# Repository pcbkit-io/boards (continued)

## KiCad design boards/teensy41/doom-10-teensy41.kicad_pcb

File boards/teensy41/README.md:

# 10 · teensy41 — Cortex-M7 at 600 MHz: Doom at full speed, Doom II too

The most capable variant: a Teensy 4.1 (NXP i.MX RT1062) on sockets behind a 3.5" 320 × 480 touch
TFT, ten buttons, CD-quality audio to headphones and a speaker, and two 18650 cells with protection,
a power-path charger on USB-C, a fuel gauge and a 5 V boost. JLCPCB assembles everything but the two
modules (and the speaker), which plug into the sockets and the connector it solders. The i.MX RT1062 is a BGA-196 crossover MCU with external flash; the Teensy module is
how hobbyists (and small products) use it without a 6-layer BGA board.

| | |
|---|---|
| Processor | Teensy 4.1: NXP i.MX RT1062, Arm **Cortex-M7** (ARMv7E-M, 6-stage dual-issue, double-precision FPU, 32 KB I + 32 KB D cache) at 600 MHz; 1 MB SRAM (512 KB tightly coupled ITCM/DTCM); 8 MB QSPI flash (FlexSPI); pads for 8 MB PSRAM (FlexSPI2); microSD socket on 4-bit SDIO (uSDHC1) |
| Display | 3.5" 320 × 480 ILI9488 + XPT2046 touch (MSP3520) on LPSPI4 (D13 SCK, D11 MOSI, D12 MISO, D10 CS, D9 DC, D8 RESET, D6 backlight PWM; touch CS D5, IRQ D4) |
| Input | 10 × 6 mm tact switches: D0–D3, D14–D17, D22, D24 |
| Sound | SAI1 I2S (D21 BCLK, D20 LRCLK, D7 TX) → **PCM5102A** → 3.5 mm jack and → **PAM8403** (shutdown on D26) → 8 Ω speaker |
| Power | 2 × 18650 Li-ion in parallel (1S2P) behind reverse-cell (AO3401A) and DW01A + FS8205A protection; USB-C (charging only, 1 A PTC fuse, TVS) → **BQ24075** power path (SYS); **MAX17048** fuel gauge (D18 SDA, D19 SCL, alert D25); **TPS61023** boost SYS → 5 V (switched by the on/off switch on its EN) → 1N5819HW → Teensy VIN (VIN and VUSB are joined on the Teensy: the diode keeps the boost and a USB host apart) |
| Programming | the Teensy's micro-USB (not the charging USB-C): **Teensy Loader** / `teensy_loader_cli` talking to its MKL02 bootloader chip (HalfKay); the program button forces it |
| Board | 172 × 112 mm, **4 layers**, four M3 holes; front: display, buttons, on/off switch, charging USB-C, charger and boost, test pads; back: Teensy (its USB at the top edge), two 18650 holders (right of the Teensy, so its microSD card comes out), audio, speaker plug (left edge), jack (right edge) |

<!-- STATUS -->
**Board status** (measured on the dev host with PCBKit's CLI): `pcbkit check`: complete — 0 errors, 0 warnings, 0 unrouted nets. 88 components, 66 nets, 769 track segments (3204 mm), 43 vias.
`analysis.run { lens: "ready" }`: Typical scenario, partly by family estimates. Nothing to fix, 1 to consider, 14 ok: weigh the warnings (tell the person about the ones that are their choice), then the board is ready to order.
`pcbkit export --format fab` succeeds without `--force`: every assembled line of the BOM has an LCSC code.
<!-- /STATUS -->

The ready lens's notes are not faults: it estimates heat with generic package limits where the
makers publish no thermal data, and reads the Teensy's and the screen's draw from their families.
Keystone 1042 holders (C5249310) are stocked in hundreds at JLCPCB: check before ordering more than
a few boards.

## Run it in the browser

Open https://app.pcbkit.io/github/pcbkit-io/doom-handheld/tree/main/boards/teensy41, open the
Laboratory and press **Build & run**: the page builds `doom/` for the i.MX RT1062's Cortex-M7
(with `DOOM1.WAD` linked into its flash), boots it the way the chip's boot ROM boots the Teensy's
flash, and draws the ILI9488's frames on the board. Play with the keyboard (arrows, F fire, Space
use, comma/period strafe, M menu, Enter) or a gamepad (`input.js`).

## Why it runs Doom

The Cortex-M7 at 600 MHz runs Doom with time to spare; the game's data, the shareware WAD, is
linked into the Teensy's 8 MB flash with the program and read in place, so no SD card is needed.
Its 1 MB of RAM holds the rest: the program's start-up makes the FlexRAM one OCRAM with OCRAM2
(1 MB from 0x2020_0000) for the engine's state, two screens and a zone heap of about 600 KB (Doom's
shareware levels need about 576 KB, measured). For that the board's copy of the engine keeps its
trigonometric tables in flash, its visplanes' rows in bytes (as Doom's original did) and changes
screens without the melt (`doom/doom_teensy.c` says where). Each frame goes to the ILI9488 in
18-bit colour (its only format over SPI), 320 × 200 in the middle of its 480 × 320, on LPSPI4 at
33 MHz: 46 ms a frame. Measured in PCBKit's simulator: the title at 4 s of device time, the demo
at 13 s.

## Power

Two 18650 Li-ion cells in Keystone 1042 holders on the back, in parallel (1S2P, 3.0–4.2 V), the
power section of `boards/rp2350-handheld` with this board's own USB-C, boost and fuel gauge:

- **Reverse cells:** an AO3401A P-MOSFET in the plus line, its gate at the cells' minus: cells put
  in backwards leave it off and the board unpowered (it conducts both ways when they are right, so
  charging goes through it too). It cannot help one cell reversed against the other: in parallel
  they would short each other, so check both against the silkscreen's + before closing a case.
- **Protection:** DW01A + FS8205A in the pack's minus: over-charge 4.3 V, over-discharge 2.4 V,
  over-current about 3 A and short circuit, for the pack. Flat-top unprotected 18650 cells fit the
  holders.
- **Charger with power path:** a TI BQ24075 from the USB-C (5.1 kΩ on CC, a 1 A resettable fuse and
  a TVS diode on VBUS), in USB500 mode (at most 500 mA from the port), 800 mA fast charge (RISET
  1.13 kΩ), input limit set by RILIM 1.18 kΩ, safety timers off (two cells in parallel charge longer
  than its longest timer; termination is by current), TS tied to 10 kΩ (no thermistor). Its output
  SYS runs the board from USB when one is plugged in and from the cells otherwise.
- **5 V and on/off:** the TPS61023 boosts SYS to 5 V for the Teensy's VIN through a 1N5819HW; the
  slide switch on the left edge drives the boost's EN (off: the Teensy unpowered, the cells still
  charging). The speaker amplifier runs from SYS, the DAC and the screen from the Teensy's 3.3 V.
- **Fuel gauge:** a MAX17048 on the cells (after the protection) reports their charge over I2C.

| State | Current (estimate) |
|---|---|
| Teensy 4.1 at 600 MHz | ~100 mA at 5 V VIN (PJRC: about 100 mA) |
| ILI9488 3.5" with backlight | ~80–100 mA at 3.3 V |
| PCM5102A + PAM8403 | 20 + 50–200 mA |
| **Typical** | **≈ 1 W → ~300 mA at 3.7 V after the boost** |

Two 3000 mAh cells → **about 20 h** (estimate). A full charge of two empty cells at 800 mA takes
about 8 h (longer from a USB 2.0 port, which the charger limits to 500 mA).

## Charging

Plug a USB-C charger into the board's USB-C at the bottom edge (charging only; it has no data). The
red LED (CHG) is on while the cells charge and goes out when they are full; the green LED (USB) is
on while USB power is present. The board plays from USB while it charges, and charges with the
switch off. Insert the cells with + at the end the back's silkscreen marks.

## Modules plugged in by hand

The assembly solders two 1x24 female sockets, one 1x14 female socket and a JST PH speaker plug;
these are bought separately:

- **U1: Teensy 4.1** (PJRC TEENSY41, with pins soldered on), on the back, components facing the
  board, its USB at the top edge; a microSD card in its socket holds the WAD.
- **DS1: 3.5" ILI9488 SPI TFT with touch, MSP3520** (14 pins), on the front.
- **J5: an 8 Ω, 1–2 W speaker** with a 2-pin JST PH lead.

## Firmware: build and flash

- **Build:** in PCBKit, the Laboratory's **Build & run** builds `doom/` (Cortex-M7, hard float, the
  kit's flash configuration block, IVT and boot data at the start of flash); then export the
  firmware (`export.run { format: "firmware" }`): `U1.hex`.
- **Flashing on arrival:** plug the Teensy's micro-USB into a computer, open the Teensy Loader (or
  run `teensy_loader_cli --mcu=TEENSY41 -w -v U1.hex`) and press the Teensy's program button: its
  MKL02 boot loader chip writes the image; nothing on the board to configure, no programmer.

## Bill of materials

Rough cost at 10 pieces (estimates): Teensy 4.1 $31.50 · 2 × 24-pin sockets $0.80 · MSP3520 3.5"
touch module $11 · PCM5102A $2.00 · PAM8403 $0.15 · jack $0.60 · BQ24075 $1.10 · DW01A, FS8205A and
AO3401A $0.25 · MAX17048 $1.60 · TPS61023 $0.60 · USB-C $0.20 · buttons $2.90 · passives $1.50 ·
two 18650 holders $9.80 · 4-layer PCB $5.00 · speaker $1.00 · microSD card $4 → **about $75**
without the cells.

<!-- BOM -->
The assembly BOM as `pcbkit export --format fab` writes it (JLCPCB assembly: LCSC codes; the modules' lines are their sockets):

| Qty | Refs | Part | LCSC | Footprint |
|---|---|---|---|---|
| 2 | BT1, BT2 | 1042 | C5249310 | BatteryHolder_Keystone_1042_1x18650 |
| 6 | C1, C3, C5, C9, C18, C21 | 100nF | C1525 | C_0402_1005Metric |
| 4 | C2, C4, C6, C22 | 10uF | C15850 | C_0805_2012Metric |
| 2 | C7, C8 | 2.2uF | C87994 | C_0805_2012Metric |
| 2 | C10, C11 | 2.2nF | C1531 | C_0402_1005Metric |
| 4 | C12, C13, C14, C16 | 1uF | C52923 | C_0402_1005Metric |
| 3 | C15, C23, C24 | 22uF | C12891 | C_1206_3216Metric |
| 1 | C17 | 470nF | C47339 | C_0402_1005Metric |
| 1 | D1 | 1N5819HW-7-F | C82544 | D_SOD-123 |
| 1 | D2 | tvs 5V | C19224 | D_SOD-323 |
| 1 | DS1 | Female header 1x14 2.54 mm | C2905420 | TFT_3.5in_ILI9488_Socket_1x14_P2.54mm |
| 1 | F1 | PTC 1000mA | C20800 | Fuse_1206_3216Metric |
| 1 | J1 | SJ1-3525N | C4991936 | Jack_3.5mm_SameSky_SJ1-352XN_Horizontal |
| 1 | J3 | USB_C_Receptacle_USB2.0_16P | C165948 | USB_C_Receptacle_USB2.0_16P |
| 1 | J5 | S2B-PH-K-S(LF)(SN) | C173752 | JST_PH_S2B-PH-K_1x02_P2.00mm_Horizontal |
| 1 | L1 | 1uH | C96955 | L_Power_6x6mm |
| 1 | Q1 | AO3401A | C15127 | SOT-23 |
| 1 | Q2 | FS8205A | C5148694 | TSSOP-8_4.4x2.93mm_P0.65mm |
| 5 | R1, R2, R3, R4, rTs | 10kohm | C25744 | R_0402_1005Metric |
| 1 | R5 | 1Mohm | C26083 | R_0402_1005Metric |
| 2 | R6, R7 | 470ohm | C25117 | R_0402_1005Metric |
| 2 | R8, R18 | 100kohm | C25741 | R_0402_1005Metric |
| 1 | R9 | 100ohm | C25076 | R_0402_1005Metric |
| 1 | R10 | 1kohm | C11702 | R_0402_1005Metric |
| 2 | R11, R12 | 5.1kohm | C25905 | R_0402_1005Metric |
| 2 | R15, R16 | 3.3kohm | C25890 | R_0402_1005Metric |
| 1 | R17 | 732kohm | C137940 | R_0402_1005Metric |
| 10 | SW1, SW2, SW3, SW4, SW5, SW6, SW7, SW8, SW9, SW10 | PTS645SM43SMTR92 LFS | C221880 | SW_Tactile_SPST_6x6mm_SMD |
| 1 | SW12 | MSK12C02 | C431540 | SW_Slide_SPDT_Shouhan_MSK12C02 |
| 2 | U1 | Female header 1x24 2.54 mm | C41376163 | Teensy41_Socket_2x24_P2.54mm_W15.24mm |
| 1 | U2 | PCM5102APWR | C107671 | TSSOP-20_4.4x6.5mm_P0.65mm |
| 1 | U3 | PAM8403DR | C17337 | SOIC-16_3.9x9.9mm_P1.27mm |
| 1 | U4 | BQ24075RGTR | C15464 | QFN-16-1EP_3x3mm_P0.5mm_EP1.68x1.68mm |
| 1 | U5 | MAX17048G+T10 | C2682616 | DFN-8-1EP_2x2mm_P0.5mm_EP0.8x1.2mm |
| 1 | U6 | TPS61023DRLR | C919459 | SOT-563 |
| 1 | U7 | DW01A | C351410 | SOT-6_1.6x2.9mm_P0.95mm |
| 2 | cBat, cSys | 4.7uF | C1779 | C_0805_2012Metric |
| 1 | cIn | 1uF | C15849 | C_0603_1608Metric |
| 1 | ledChg | red | C2286 | LED_0603_1608Metric |
| 1 | ledPg | green | C12624 | LED_0603_1608Metric |
| 2 | rChg, rPg | 1.5kohm | C25867 | R_0402_1005Metric |
| 1 | rIlim | 1.18kohm | C270651 | R_0402_1005Metric |
| 1 | rIset | 1.13kohm | C67014 | R_0402_1005Metric |
<!-- /BOM -->

## What PCBKit's engine must model to simulate it faithfully

- **Core:** **ARMv7E-M with FPv5-D16** (double precision), plus the M7's **caches** (CCR, cache
  maintenance by address: the SDK cleans/invalidates around DMA) and **TCM** (ITCM/DTCM at 0x0 /
  0x2000_0000 with FlexRAM banks configured by `IOMUXC_GPR`); MPU regions the SDK programs.
- **Interrupt controller:** NVIC with 160 lines; SysTick; the GPT/PIT timers Teensyduino uses.
- **Boot ROM:** the i.MX RT boot ROM's **serial NOR boot**: read the FCB at 0x6000_0000 to configure
  FlexSPI, then the IVT and boot data, then jump; the image format is that header, not ELF.
- **Clocks (CCM):** ARM PLL to 600 MHz, the dividers for IPG/PERCLK, LPSPI and SAI root clocks;
  the DCDC voltage step Teensyduino performs before raising the clock.
- **Peripherals:** **IOMUXC** pin mux (every pad has a mux register and a pad-control register: the
  pin-mux table from NXP's SVD), GPIO1–9 (fast GPIO6–9 aliases), LPSPI4 + **eDMA with DMAMUX**,
  **SAI1** (I2S) + eDMA, LPI2C1, **uSDHC1** (SD 4-bit with ADMA2 descriptors), USB OTG (the bootloader
  is a separate chip: flashing can be modelled as writing the image directly).
- **Board:** ILI9488 (18-bit pixel format over SPI) + XPT2046, SD card in SD mode, PCM5102A, BQ24075,
  MAX17048, two 18650 cells as a discharge curve, a boost into VIN behind a diode.

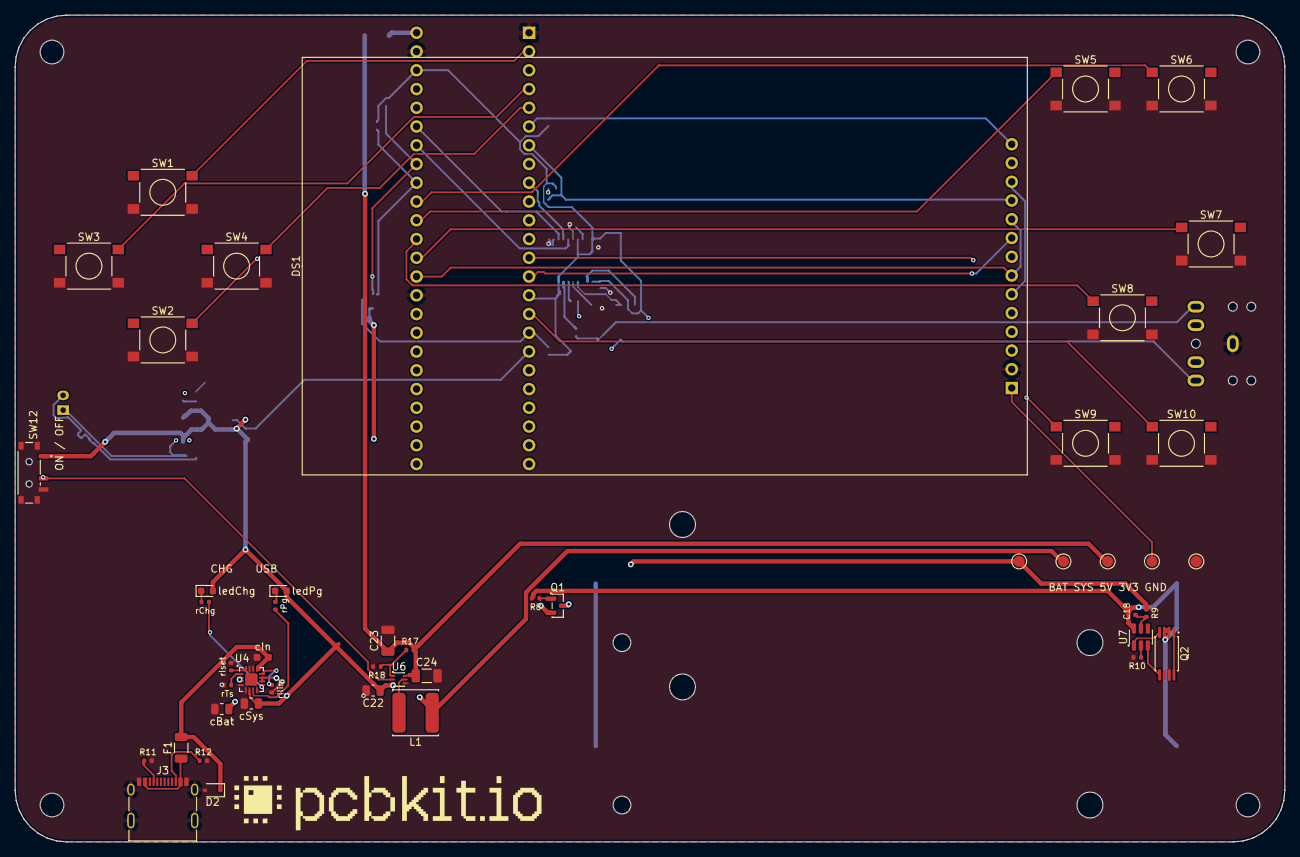
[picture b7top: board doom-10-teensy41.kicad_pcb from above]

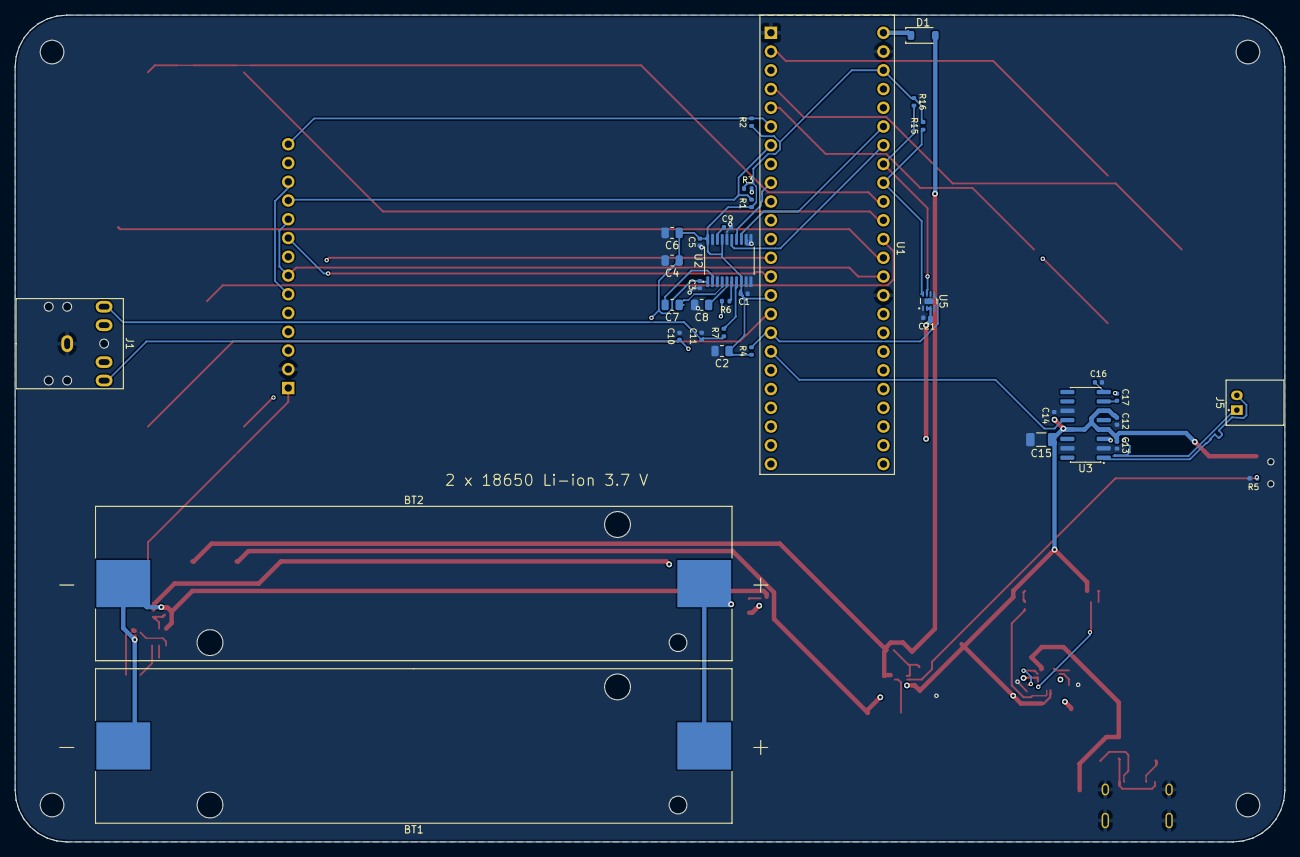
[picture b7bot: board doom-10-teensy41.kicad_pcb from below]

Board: 4 copper layers, 172.0 x 112.0 mm, 88 parts (36 on the bottom side), 66 nets.

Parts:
BT1, BT2: 1042; BatteryHolder_Keystone_1042_1x18650
C1, C3, C5, C9, C18, C21: 100nF; C_0402_1005Metric
C2, C4, C6, C22: 10uF; C_0805_2012Metric
C7, C8: 2.2uF; C_0805_2012Metric
C10, C11: 2.2nF; C_0402_1005Metric
C12, C13, C14, C16: 1uF; C_0402_1005Metric
C15, C23, C24: 22uF; C_1206_3216Metric
C17: 470nF; C_0402_1005Metric
D1: 1N5819HW-7-F; D_SOD-123
D2: tvs 5V; D_SOD-323
DS1: MSP3520 3.5in 320x480 SPI TFT module with touch (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; TFT_3.5in_ILI9488_Socket_1x14_P2.54mm
F1: PTC 1000mA; Fuse_1206_3216Metric
H1, H2, H3, H4: MountingHole_3.2mm_M3
J1: SJ1-3525N; Jack_3.5mm_SameSky_SJ1-352XN_Horizontal
J3: USB_C_Receptacle_USB2.0_16P
J5: S2B-PH-K-S(LF)(SN); JST_PH_S2B-PH-K_1x02_P2.00mm_Horizontal
L1: 1uH; L_Power_6x6mm
Q1: AO3401A; SOT-23
Q2: FS8205A; TSSOP-8_4.4x2.93mm_P0.65mm
R1, R2, R3, R4: 10kohm; R_0402_1005Metric
R5: 1Mohm; R_0402_1005Metric
R6, R7: 470ohm; R_0402_1005Metric
R8, R18: 100kohm; R_0402_1005Metric
R9: 100ohm; R_0402_1005Metric
R10: 1kohm; R_0402_1005Metric
R11, R12: 5.1kohm; R_0402_1005Metric
R15, R16: 3.3kohm; R_0402_1005Metric
R17: 732kohm; R_0402_1005Metric
SW1, SW2, SW3, SW4, SW5, SW6, SW7, SW8, SW9, SW10: PTS645SM43SMTR92 LFS; SW_Tactile_SPST_6x6mm_SMD
SW12: MSK12C02; SW_Slide_SPDT_Shouhan_MSK12C02
U1: TEENSY41; Teensy41_Socket_2x24_P2.54mm_W15.24mm
U2: PCM5102APWR; TSSOP-20_4.4x6.5mm_P0.65mm
U3: PAM8403DR; SOIC-16_3.9x9.9mm_P1.27mm
U4: BQ24075RGTR; QFN-16-1EP_3x3mm_P0.5mm_EP1.68x1.68mm
U5: MAX17048G+T10; DFN-8-1EP_2x2mm_P0.5mm_EP0.8x1.2mm
U6: TPS61023DRLR; SOT-563
U7: DW01A; SOT-6_1.6x2.9mm_P0.95mm
cBat: 4.7uF; C_0805_2012Metric
cIn: 1uF; C_0603_1608Metric
cSys: 4.7uF; C_0805_2012Metric
ledChg: red; LED_0603_1608Metric
ledPg: green; LED_0603_1608Metric
logo: Logo_PCBKit_pcbkit.io
rChg: 1.5kohm; R_0402_1005Metric
rIlim: 1.18kohm; R_0402_1005Metric
rIset: 1.13kohm; R_0402_1005Metric
rPg: 1.5kohm; R_0402_1005Metric
rTs: 10kohm; R_0402_1005Metric
tpBat: TestPoint_Round_D1.5mm
tpGnd: TestPoint_Round_D1.5mm
tpSys: TestPoint_Round_D1.5mm
tpV3, tpV5: TestPoint_Round_D1.5mm

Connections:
AMP_SD: U1.18, U3.12
BAT: C21.1, Q1.2, R9.1, U4.2, U4.3, U5.2, U5.3, cBat.1, tpBat.1
BAT_IN: BT1.2, BT2.2, Q1.3
BOOST_EN: R5.1, SW12.2, U6.2
CELL_N: BT1.1, BT2.1, C18.2, Q2.2, Q2.3, R8.2, U7.6
CHG_LED: ledChg.1, rChg.2
CHG_N: U4.9, rChg.1
DAC_LDO: C9.1, U2.18
DAC_VNEG: C8.1, U2.5
DOWN: SW2.1, SW2.2, U1.3
ENTER: SW10.1, SW10.2, U1.16
FIRE: SW7.1, SW7.2, U1.37
FUEL_ALRT: R4.2, U1.17, U5.5
GND: C1.2, C2.2, C3.2, C4.2, C5.2, C6.2, C8.2, C9.2, C10.2, C11.2, C12.2, C13.2, C14.2, C15.2, C16.2, C21.2, C22.2, C23.2, C24.2, D2.2, DS1.2, J1.1, J3.A1, J3.B1, J3.S1, Q2.6, Q2.7, R5.2, R10.2, R11.2, R12.2, R18.2, SW1.3, SW1.4, SW2.3, SW2.4, SW3.3, SW3.4, SW4.3, SW4.4, SW5.3, SW5.4, SW6.3, SW6.4, SW7.3, SW7.4, SW8.3, SW8.4, SW9.3, SW9.4, SW10.3, SW10.4, SW12.3, SW12.4, U1.1, U1.26, U1.39, U2.3, U2.9, U2.10, U2.11, U2.12, U2.16, U2.19, U3.2, U3.11, U3.15, U4.4, U4.5, U4.8, U4.14, U4.15, U4.17, U5.1, U5.4, U5.6, U5.9, U6.4, cBat.2, cIn.2, cSys.2, rIlim.2, rIset.2, rTs.2, tpGnd.1
I2S_BCK: U1.30, U2.13
I2S_DIN: U1.9, U2.14
I2S_LRCK: U1.31, U2.15
ILIM: U4.12, rIlim.1
ISET: U4.16, rIset.1
LCD_BL: DS1.8, U1.8
LCD_CS: DS1.3, R3.2, U1.12
LCD_DC: DS1.5, U1.11
LCD_RST: DS1.4, U1.10
LEFT: SW3.1, SW3.2, U1.4
LINE_L: C10.1, C17.1, J1.2, R6.2
LINE_R: C11.1, J1.3, R7.1
MENU: SW9.1, SW9.2, U1.29
MISO: DS1.9, DS1.13, U1.14
MOSI: DS1.6, DS1.12, U1.13
unnamed: C7.2, U2.2
unnamed: C7.1, U2.4
unnamed: C16.1, U3.8
unnamed: C17.2, U3.7
unnamed: C18.1, R9.2, U7.5
unnamed: L1.2, U6.5
unnamed: Q2.4, U7.1
unnamed: Q2.5, U7.3
unnamed: R6.1, U2.6
unnamed: R7.2, U2.7
unnamed: R10.1, U7.2
unnamed: R17.1, R18.1, U6.1
PG_LED: ledPg.1, rPg.1
PG_N: U4.7, rPg.2
RIGHT: SW4.1, SW4.2, U1.5
SCK: DS1.7, DS1.10, U1.38
SCL: R16.2, U1.32, U5.7
SDA: R15.1, U1.33, U5.8
SPK_N: J5.1, U3.3
SPK_P: J5.2, U3.1
STRAFE_L: SW5.1, SW5.2, U1.35
STRAFE_R: SW6.1, SW6.2, U1.34
SYS: C12.1, C13.1, C14.1, C15.1, C22.1, L1.1, SW12.1, U3.4, U3.6, U3.13, U4.6, U4.10, U4.11, U6.3, cSys.1, ledChg.2, ledPg.2, tpSys.1
TS: U4.1, rTs.1
T_CS: DS1.11, R1.2, U1.7
T_IRQ: DS1.14, R2.2, U1.6
U7Support/DRAIN: Q2.1, Q2.8
UP: SW1.1, SW1.2, U1.2
USE: SW8.1, SW8.2, U1.36
V3: C1.1, C2.1, C3.1, C4.1, C5.1, C6.1, DS1.1, R1.1, R2.1, R3.1, R4.1, R15.2, R16.1, U1.15, U1.27, U2.1, U2.8, U2.17, U2.20, tpV3.1
V5: C23.1, C24.1, D1.2, R17.2, U6.6, tpV5.1
VBUS: D2.1, F1.2, U4.13, cIn.1
VIN: D1.1, U1.25
reversed/gate: Q1.1, R8.1
usb/cc1: J3.A5, R11.1
usb/cc2: J3.B5, R12.1
usb/raw: F1.1, J3.A4, J3.B4

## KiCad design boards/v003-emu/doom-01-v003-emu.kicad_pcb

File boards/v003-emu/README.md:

# 01 · v003-emu — Doom on a 10-cent RISC-V, by emulation

The most primitive variant: a WCH CH32V003 cannot hold Doom (2 KB of RAM), so it does not try.
Its firmware is a small RV32IMA interpreter; the real program — Doom built for a plain RV32 machine
— lives in an 8 MB SPI PSRAM and boots from a 16 MB SPI flash. It is the "Linux on an 8-bit AVR"
trick applied to Doom: slow (well under one frame per second, estimate below), but every part is a
real, orderable chip, and it is the clearest test of whether PCBKit's engine models *buses* rather
than *programs*.

| | |
|---|---|
| Processor | WCH CH32V003F4P6, QingKe V2A core: RISC-V **RV32EC** (16 registers, compressed) + WCH's XW byte/halfword extension, 48 MHz (24 MHz HSI × 2 PLL), 2 KB SRAM, 16 KB flash, TSSOP-20 |
| Memory | APS6404L-3SQR 8 MB PSRAM (guest RAM) and W25Q128JV 16 MB NOR flash (guest kernel + WAD), both on SPI1 (PC5/PC6/PC7) with their own chip selects (PC0, PC4) |
| Display | Nokia 5110 module, PCD8544, 84 × 48 monochrome, SPI shared with the memories (CS PC3, D/C PC2), reset by RC at power-up |
| Input | 8 tact switches (5.1 mm) to GND, internal pull-ups: PD0, PD2–PD6, PA1, PA2 (the crystal pins are free: the HSI runs the chip) |
| Sound | passive piezo on PC1 (TIM2 CH4 remap) |
| Power | 2 × 18650 Li-ion in parallel (1S2P) behind reverse-cell (AO3401A) and DW01A + FS8205A protection; BQ24075 charger with power path from a USB-C port (fuse, TVS); SYS → AP2112K-3.3 LDO, its enable on the slide switch |
| Programming | WCH single-wire debug (SDI) on PD1: J2, a 3-pin header (3V3, SWIO, GND) at the right edge of the back for a WCH-LinkE |
| Board | 96 × 92 mm, 2 layers, four M3 holes; front: LCD, buttons, USB-C, charger, switch, test pads; back: two 18650 holders, the processor and its memories, piezo, J2 |

<!-- STATUS -->
**Board status** (measured on the dev host with PCBKit's CLI): `pcbkit check`: complete — 0 errors, 0 warnings, 0 unrouted nets. 67 components, 46 nets, 439 track segments (1295 mm), 38 vias.
`analysis.run { lens: "ready" }`: Typical scenario, partial. Nothing to fix, 1 to consider, 15 ok: weigh the warnings (tell the person about the ones that are their choice), then the board is ready to order.
`pcbkit export --format fab` succeeds without `--force`: every assembled line of the BOM has an LCSC code.
<!-- /STATUS -->

## Run it in the browser

Open https://app.pcbkit.io/github/pcbkit-io/doom-handheld/tree/main/boards/v003-emu, open the
Laboratory and press **Build & run**: the page builds both programs — `emu/` for the CH32V003
(RV32EC) and `doom/` for the computer it emulates (pcbkit-virt, with `DOOM1.WAD` linked in) — puts
the second in the W25Q128 and runs the board. Until the first frame the LCD shows Doom's start-up
messages; the title screen comes after about three minutes of device time, then the demo.

## Why it can (barely) run Doom

The CH32V003's job is only to be a CPU for an emulated one (`emu/`):

1. Its firmware (15.6 KB of its 16 KB flash) is an RV32IMAC interpreter (`emu/rvemu.c`) with a
   direct-mapped write-back cache of 32 lines × 16 bytes in its 2 KB of SRAM.
2. The guest (`doom/`: Doom for pcbkit-virt, an ELF file) is in the W25Q128: its code and
   constants, the WAD linked into them, are read where they lie; its writable segment is copied
   into the PSRAM at boot.
3. Guest loads and stores go through the cache; a miss is one SPI transaction (command, 24-bit
   address and 16 bytes at 24 MHz, 6.7 µs with the chip selected: inside the PSRAM's 8 µs limit).
4. Each guest frame (320 × 200, 8-bit) is scaled to 84 × 48 with ordered dithering and sent to
   the PCD8544; its start-up messages are shown on the glass until then, and a stop says why.

**Speed, measured in PCBKit's simulator** (instruction-accurate CH32V003 at 48 MHz, the memories'
SPI timing): Doom's start-up messages from the first second, its title screen at about 200 s of
device time, the demo at 300 s, then a frame every several seconds. It is a demonstration
board, not a game console — and the reason it is variant 01.

## Power

| State | Current at 3.3 V (estimate) |
|---|---|
| CH32V003 at 48 MHz | ~5 mA |
| PSRAM active (SPI, low clock) | ~3–5 mA (datasheet: 5.5 mA typ at 133 MHz) |
| W25Q128 (only while booting) | ~10 mA |
| PCD8544 + backlight through 330 Ω | ~0.3 mA + ~4 mA |
| **Total** | **~15–20 mA ≈ 60 mW** |

Two 18650 Li-ion cells in Keystone 1042 holders on the back, in parallel (1S2P, 3.0–4.2 V). From
the cells to the chips:

- **Reverse cells:** an AO3401A P-MOSFET in the plus line, its gate at the cells' minus: cells put
  in backwards leave it off and the board unpowered (it conducts both ways when they are right, so
  charging goes through it too). It cannot help one cell reversed against the other: in parallel
  they would short each other, so check both against the silkscreen's + before closing a case.
- **Protection:** DW01A + FS8205A in the pack's minus: over-charge 4.3 V, over-discharge 2.4 V,
  over-current about 3 A and short circuit, for the pack. Flat-top unprotected 18650 cells fit
  the holders.
- **USB-C input:** a power-only receptacle (5.1 kΩ on CC1 and CC2: any USB-C charger or computer
  gives 5 V), a 750 mA resettable fuse (nSMD075) and a 5 V TVS diode (SMF5.0A) before the charger.
- **Charger with power path:** a TI BQ24075 in USB500 mode (at most 500 mA from the port), ISET
  for 800 mA (RISET 1.13 kΩ), RILIM 1.18 kΩ, safety timers off (two cells in parallel charge longer
  than its longest timer; termination is by current), TS tied to 10 kΩ (no thermistor). A linear
  charger passes on at most what it takes in, so from USB the cells charge at up to about 500 mA.
  Its output SYS runs the board from USB when one is plugged in and from the cells otherwise.
- **3.3 V:** an AP2112K-3.3 LDO from SYS (the old TPS61023 boost cannot make 3.3 V from a Li-ion
  cell above it). At this board's 20 mA its dropout is a few mV, so 3.3 V holds down to about
  3.3 V on the cells and then follows them; every chip here runs from 2.7 V.
- **On/off:** the slide switch at the top edge drives the LDO's enable (1 MΩ pulls it off); the
  charger charges with the switch off. Off, the board draws only the charger's and the protection's
  few µA.

Two 3000 mAh cells (about 22 Wh) at 60 mW: **about 300 h** of (very slow) play (estimate). A
full charge of two empty cells from USB at about 500 mA takes about 12 h.

## Charging

Plug any USB-C charger or computer into J1 at the left edge. The red LED (CHG) is on while the
cells charge and goes out when they are full; the green LED (USB) is on while USB power is
present. The board runs from USB while it charges, switched on or off. Insert the cells with +
at the end the back's silkscreen marks.

## Modules plugged in by hand

The assembly solders a 1x8 female socket for the display; the module is bought separately:

- **DS1: Nokia 5110 LCD module** (PCD8544, 84 × 48, the common red board with an 8-pin header:
  RST, CE, DC, DIN, CLK, VCC, BL, GND in that order), its pins soldered on as it comes, plugged in
  on the front. Boards with another pin order exist: check the order on its silkscreen against
  the board's before plugging it in.

## Firmware: build and flash

- **Build:** in PCBKit, the Laboratory's **Build & run** builds both programs (the CH32V003's with
  RV32EC, ilp32e, -Os; the guest for RV32IMAC with the WAD); then export the firmware
  (`export.run { format: "firmware" }`): `U1.bin` for the CH32V003 and `U3.bin` for the W25Q128.
- **The CH32V003, on arrival:** a WCH-LinkE (about $5, USB) on J2: its 3V3, SWIO and GND to J2's
  (marked on the back). Then `minichlink -w U1.bin flash -b` (ch32v003fun) or WCH-LinkUtility.
- **The W25Q128 (the guest):** hold MENU while switching on: the emulator lets go of the SPI bus
  (every pin an input) and waits, so a USB SPI programmer (CH341A) with a SOIC-8 clip on the
  W25Q128 writes it in place: `flashrom -p ch341a_spi -w U3.bin`. Switch off and on: Doom boots.

## Bill of materials

Key parts and a rough cost at 10 pieces (estimates, LCSC/AliExpress prices of 2026):
CH32V003F4P6 $0.30 · APS6404L $1.20 · W25Q128JV $1.00 · Nokia 5110 module $2.50 ·
switch $0.10 · buttons 8 × $0.05 · charger, protection, LDO, USB-C and passives $2.20 · two 18650
holders $9.80 · PCB (2-layer, 96 × 92) $1.50 → **about $20 per unit** without the cells.

<!-- BOM -->
The assembly BOM as `pcbkit export --format fab` writes it (JLCPCB assembly: LCSC codes; the modules' lines are their sockets):

| Qty | Refs | Part | LCSC | Footprint |
|---|---|---|---|---|
| 2 | BT1, BT2 | 1042 | C5249310 | BatteryHolder_Keystone_1042_1x18650 |
| 1 | BZ1 | GPC12075YB-5V4000 | C252948 | Buzzer_D12.0mm_H7.5mm_P6.50mm |
| 7 | C1, C2, C3, C5, C7, C8, C9 | 100nF | C1525 | C_0402_1005Metric |
| 3 | C4, C6, C10 | 1uF | C52923 | C_0402_1005Metric |
| 1 | D1 | tvs 5V | C284108 | D_SOD-123 |
| 1 | DS1 | Nokia 5110 84x48 LCD module (PCD8544): connector (8-pin) | C2905417 | PinHeader_1x08_P2.54mm_Vertical |
| 1 | F1 | PTC 680mA | C70078 | Fuse_1206_3216Metric |
| 1 | J1 | USB_C_Receptacle_USB2.0_16P | C165948 | USB_C_Receptacle_USB2.0_16P |
| 1 | J2 | PinHeader_1x03_P2.54mm_Vertical | C49257 | PinHeader_1x03_P2.54mm_Vertical |
| 1 | Q1 | AO3401A | C15127 | SOT-23 |
| 1 | Q2 | FS8205A | C5148694 | TSSOP-8_4.4x2.93mm_P0.65mm |
| 7 | R1, R2, R7, R8, R9, R10, rTs | 10kohm | C25744 | R_0402_1005Metric |
| 1 | R3 | 330ohm | C23138 | R_0603_1608Metric |
| 1 | R4 | 1Mohm | C26083 | R_0402_1005Metric |
| 1 | R5 | 100kohm | C25741 | R_0402_1005Metric |
| 1 | R6 | 100ohm | C25076 | R_0402_1005Metric |
| 1 | R11 | 1kohm | C11702 | R_0402_1005Metric |
| 2 | R12, R13 | 5.1kohm | C25905 | R_0402_1005Metric |
| 8 | SW1, SW2, SW3, SW4, SW5, SW6, SW7, SW8 | TS-1187A-B-A-B | C318884 | SW_Tactile_SPST_5.1x5.1mm_SMD |
| 1 | SW9 | MSK12C02 | C431540 | SW_Slide_SPDT_Shouhan_MSK12C02 |
| 1 | U1 | CH32V003F4P6 | C5187096 | TSSOP-20_4.4x6.5mm_P0.65mm |
| 1 | U2 | APS6404L-3SQR-SN | C5333729 | SOIC-8_3.9x4.9mm_P1.27mm |
| 1 | U3 | W25Q128JVSIQ | C97521 | SOIC-8_5.23x5.28mm_P1.27mm |
| 1 | U4 | AP2112K-3.3TRG1 | C51118 | SOT-23-5 |
| 1 | U5 | DW01A | C351410 | SOT-6_1.6x2.9mm_P0.95mm |
| 1 | U6 | BQ24075RGTR | C15464 | QFN-16-1EP_3x3mm_P0.5mm_EP1.68x1.68mm |
| 2 | cBat, cSys | 4.7uF | C1779 | C_0805_2012Metric |
| 1 | cIn | 1uF | C15849 | C_0603_1608Metric |
| 1 | ledChg | red | C2286 | LED_0603_1608Metric |
| 1 | ledPg | green | C12624 | LED_0603_1608Metric |
| 2 | rChg, rPg | 1.5kohm | C25867 | R_0402_1005Metric |
| 1 | rIlim | 1.18kohm | C270651 | R_0402_1005Metric |
| 1 | rIset | 1.13kohm | C67014 | R_0402_1005Metric |
<!-- /BOM -->

## What PCBKit's engine must model to simulate it faithfully

- **Core:** RV32EC (16 registers; the current RV32IMAC core with a register-count switch and E-ABI
  traps on x16–x31) plus WCH's XW extension (compressed byte/halfword loads and stores) and the
  V2A's lack of M (multiply in software).
- **Interrupt controller:** WCH PFIC (a CLIC-like controller with vector table, hardware stacking
  "HPE" and nesting), SysTick in the core's address space.
- **Boot:** the V003 boots from user flash at 0x0000_0000 (a boot area with WCH's bootloader is
  optional); option bytes; no ROM image format.
- **Clocks:** HSI 24 MHz ×2 PLL, AHB prescaler; a cycle model matters here (the speed estimate is
  all about cycles per guest instruction and SPI time).
- **Peripherals the firmware uses:** SPI1 (mode 0, 8-bit, polling), GPIO (GPIOA/C/D with CFGLR
  4-bit mode fields), AFIO remap (PC1 TIM2), TIM2 PWM, the SDI debug transport for flashing.
- **External devices on SPI with chip selects:** an APS6404L model (03h/0Bh/02h/38h/EBh commands,
  QPI enter/exit, 8 MB array) and a W25Q128 model (read, page program, sector erase, status), plus
  a PCD8544 display model (D/C pin, 84 × 48 RAM, addressing modes). The current `Link::spi` moves
  one byte without a chip select: these devices need **CS and D/C framing** on the link.
- **Board:** two 18650 cells as a discharge curve behind the charger's power path and an LDO.

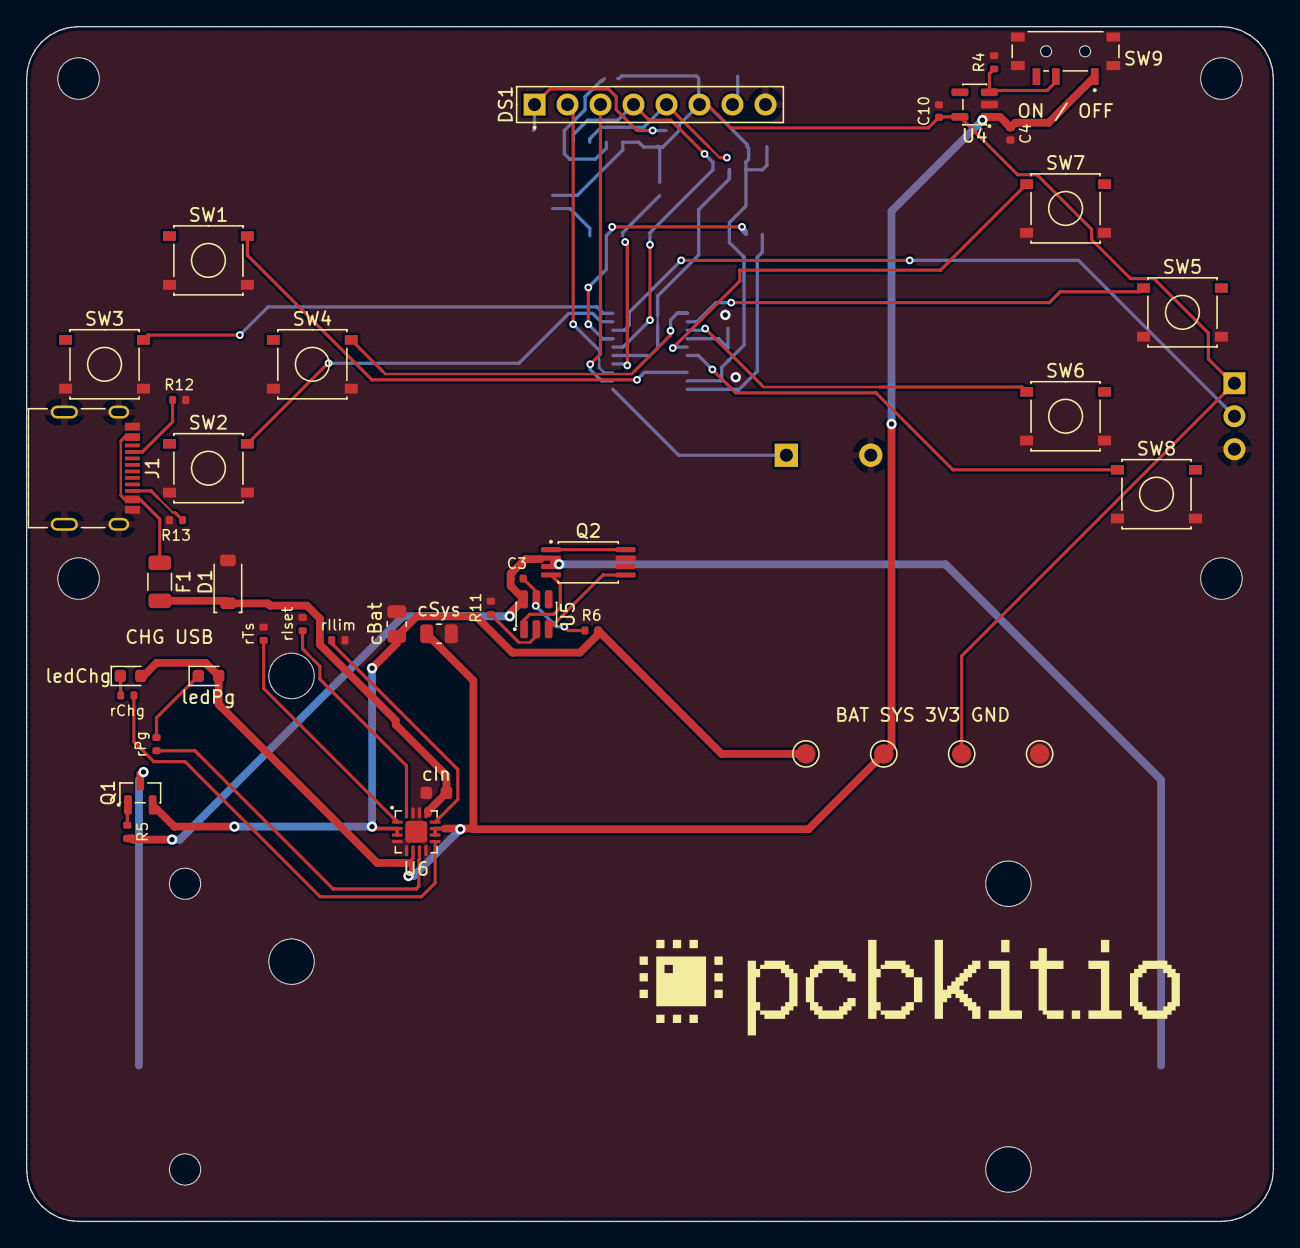
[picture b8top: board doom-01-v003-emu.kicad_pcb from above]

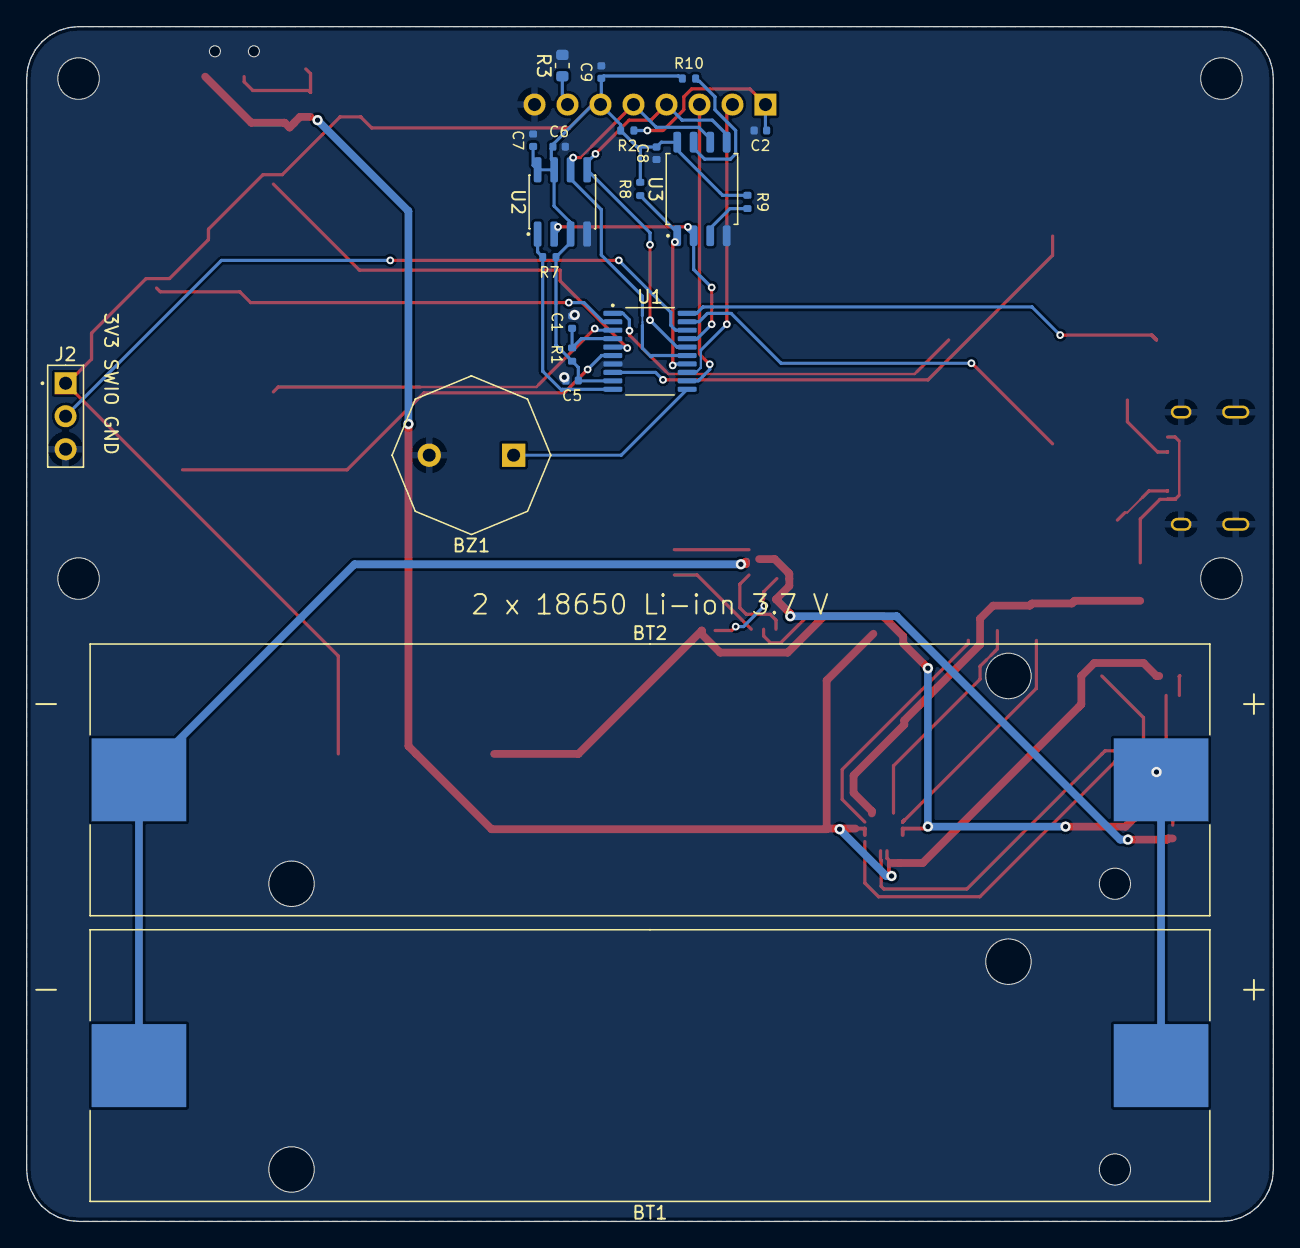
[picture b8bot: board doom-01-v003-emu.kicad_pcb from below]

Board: 2 copper layers, 96.0 x 92.0 mm, 67 parts (21 on the bottom side), 46 nets.

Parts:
BT1, BT2: 1042; BatteryHolder_Keystone_1042_1x18650
BZ1: GPC12075YB-5V4000; Buzzer_D12.0mm_H7.5mm_P6.50mm
C1, C2, C3, C5, C7, C8, C9: 100nF; C_0402_1005Metric
C4, C6, C10: 1uF; C_0402_1005Metric
D1: tvs 5V; D_SOD-123
DS1: Nokia 5110 84x48 LCD module (PCD8544): connector 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; PinHeader_1x08_P2.54mm_Vertical
F1: PTC 680mA; Fuse_1206_3216Metric
H1, H2, H3, H4: MountingHole_3.2mm_M3
J1: USB_C_Receptacle_USB2.0_16P
J2: PinHeader_1x03_P2.54mm_Vertical
Q1: AO3401A; SOT-23
Q2: FS8205A; TSSOP-8_4.4x2.93mm_P0.65mm
R1, R2, R7, R8, R9, R10: 10kohm; R_0402_1005Metric
R3: 330ohm; R_0603_1608Metric
R4: 1Mohm; R_0402_1005Metric
R5: 100kohm; R_0402_1005Metric
R6: 100ohm; R_0402_1005Metric
R11: 1kohm; R_0402_1005Metric
R12, R13: 5.1kohm; R_0402_1005Metric
SW1, SW2, SW3, SW4, SW5, SW6, SW7, SW8: TS-1187A-B-A-B; SW_Tactile_SPST_5.1x5.1mm_SMD
SW9: MSK12C02; SW_Slide_SPDT_Shouhan_MSK12C02
U1: CH32V003F4P6; TSSOP-20_4.4x6.5mm_P0.65mm
U2: APS6404L-3SQR-SN; SOIC-8_3.9x4.9mm_P1.27mm
U3: W25Q128JVSIQ; SOIC-8_5.23x5.28mm_P1.27mm
U4: AP2112K-3.3TRG1; SOT-23-5
U5: DW01A; SOT-6_1.6x2.9mm_P0.95mm
U6: BQ24075RGTR; QFN-16-1EP_3x3mm_P0.5mm_EP1.68x1.68mm
cBat: 4.7uF; C_0805_2012Metric
cIn: 1uF; C_0603_1608Metric
cSys: 4.7uF; C_0805_2012Metric
ledChg: red; LED_0603_1608Metric
ledPg: green; LED_0603_1608Metric
logo: Logo_PCBKit_pcbkit.io
rChg: 1.5kohm; R_0402_1005Metric
rIlim: 1.18kohm; R_0402_1005Metric
rIset: 1.13kohm; R_0402_1005Metric
rPg: 1.5kohm; R_0402_1005Metric
rTs: 10kohm; R_0402_1005Metric
tpBat: TestPoint_Round_D1.5mm
tpGnd: TestPoint_Round_D1.5mm
tpSys: TestPoint_Round_D1.5mm
tpV3: TestPoint_Round_D1.5mm

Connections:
BAT: Q1.2, R6.2, U6.2, U6.3, cBat.1, tpBat.1
BAT_IN: BT1.2, BT2.2, Q1.3
BUZZ: BZ1.1, U1.11
CELL_N: BT1.1, BT2.1, C3.1, Q2.2, Q2.3, R5.2, U5.6
CHG_LED: ledChg.1, rChg.2
CHG_N: U6.9, rChg.1
DOWN: SW2.1, SW2.2, U1.19
FIRE: SW5.1, SW5.2, U1.2
GND: BZ1.2, C1.2, C2.2, C4.2, C5.2, C6.2, C7.2, C8.2, C9.2, C10.2, D1.2, DS1.8, J1.A1, J1.B1, J1.S1, J2.3, Q2.6, Q2.7, R3.2, R4.2, R11.2, R12.2, R13.2, SW1.3, SW1.4, SW2.3, SW2.4, SW3.3, SW3.4, SW4.3, SW4.4, SW5.3, SW5.4, SW6.3, SW6.4, SW7.3, SW7.4, SW8.3, SW8.4, SW9.4, U1.7, U2.4, U3.4, U4.2, U6.4, U6.5, U6.8, U6.14, U6.15, U6.17, cBat.2, cIn.2, cSys.2, rIlim.2, rIset.2, rTs.2, tpGnd.1
ILIM: U6.12, rIlim.1
ISET: U6.16, rIset.1
LCD_BL: DS1.7, R3.1
LCD_CS: DS1.2, U1.13
LCD_DC: DS1.3, U1.12
LCD_RST: C2.1, DS1.1, R2.1
LDO_EN: R4.1, SW9.2, U4.3
LEFT: SW3.1, SW3.2, U1.20
MENU: SW8.1, SW8.2, U1.6
MISO: U1.17, U2.2, U3.2
MOSI: DS1.4, U1.16, U2.5, U3.5
NRST: C1.1, R1.2, U1.4
unnamed: C3.2, R6.1, U5.5
unnamed: Q2.4, U5.1
unnamed: Q2.5, U5.3
unnamed: R9.2, U3.3
unnamed: R10.2, U3.7
unnamed: R11.1, U5.2
PG_LED: ledPg.1, rPg.2
PG_N: U6.7, rPg.1
RAM_CS: R7.2, U1.10, U2.1
RIGHT: SW4.1, SW4.2, U1.1
ROM_CS: R8.1, U1.14, U3.1
SCK: DS1.5, U1.15, U2.6, U3.6
STRAFE: SW7.1, SW7.2, U1.5
SWIO: J2.2, U1.18
SYS: C4.1, SW9.1, U4.1, U6.6, U6.10, U6.11, cSys.1, ledChg.2, ledPg.2, tpSys.1
TS: U6.1, rTs.1
U5Support/DRAIN: Q2.1, Q2.8
UP: SW1.1, SW1.2, U1.8
USE: SW6.1, SW6.2, U1.3
V3: C5.1, C6.1, C7.1, C8.1, C9.1, C10.1, DS1.6, J2.1, R1.1, R2.2, R7.1, R8.2, R9.1, R10.1, U1.9, U2.3, U2.7, U2.8, U3.8, U4.5, tpV3.1
VBUS: D1.1, F1.2, U6.13, cIn.1
reversed/gate: Q1.1, R5.1
usb/cc1: J1.A5, R12.1
usb/cc2: J1.B5, R13.1
usb/raw: F1.1, J1.A4, J1.B4

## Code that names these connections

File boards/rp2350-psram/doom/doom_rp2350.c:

/* Doom's platform layer for doom-07: a bare RP2350A (RISC-V cores) with a 16 MiB flash and an
 * 8 MiB PSRAM on QMI chip select 1 (GPIO8), a 2.0" ST7789 240 × 320 IPS on SPI0 and ten buttons.
 * An ordinary program on the chip's devices:
 *
 *   SPI0 SCK GPIO18, TX GPIO19; display CS GPIO17, D/C GPIO16, RESET GPIO20, backlight GPIO21
 *   buttons to ground, pulled up: forward GPIO0, back 1, left 2, right 3, fire 4, use 5,
 *   strafe left 9, strafe right 15, menu 25, enter 26
 *   no console: GPIO0 and GPIO1 are buttons
 *
 * Each frame converts the 8-bit screen through Doom's palette to RGB565 and writes it to the
 * panel's 320 × 200 window (rows 20…219 of the landscape 320 × 240). The game's data, the
 * shareware DOOM1.WAD, is linked into flash (the processor's `data` in the design) and read in
 * place; the zone heap and the screens live in PSRAM. Waiting for the next tic sleeps
 * until a timer alarm. Audio and saved games are absent. The engine is sysprog21/doom_riscv
 * (GPL-2.0), unchanged at its pinned revision. */
#include <stdarg.h>
#include <stdint.h>
#include <stdio.h>
#include <stdlib.h>
#include <string.h>
#include <pcbkit/rp2350.h>
#include <pcbkit/runtime.h>
#include "doomdef.h"
#include "doomstat.h"
#include "d_main.h"
#include "i_system.h"
#include "i_video.h"
#include "v_video.h"

const struct pcbkit_board pcbkit_board = {
    .xosc_hz = 12000000, .pll_fbdiv = 125, .pll_postdiv1 = 5, .pll_postdiv2 = 2,
    .psram_cs = 8, .uart_tx = -1, .uart_rx = -1,
};

#define LCD_CS 17
#define LCD_DC 16
#define LCD_RESET 20
#define LCD_BACKLIGHT 21
#define BUTTONS 10u
/* forward, back, left, right, fire, use, strafe left, strafe right, menu, enter */
static const uint8_t button_pins[BUTTONS] = {0, 1, 2, 3, 4, 5, 9, 15, 25, 26};
#define TIC_US (1000000u / TICRATE)

static uint64_t origin;
static uint32_t held;
static uint16_t palette565[256];

static void lcd_command(uint8_t command, const uint8_t *data, size_t n) {
    pcbkit_gpio_put(LCD_CS, 0);
    pcbkit_gpio_put(LCD_DC, 0);
    pcbkit_spi_write(SPI0, &command, 1);
    pcbkit_spi_wait(SPI0); /* D/C must not change under the command byte */
    pcbkit_gpio_put(LCD_DC, 1);
    pcbkit_spi_write(SPI0, data, n);
    pcbkit_spi_wait(SPI0);
    pcbkit_gpio_put(LCD_CS, 1);
}

static void sleep_ms(unsigned ms) { pcbkit_sleep_until(pcbkit_time_us() + ms * 1000u); }

static void lcd_start(void) {
    pcbkit_gpio_output(LCD_CS, 1);
    pcbkit_gpio_output(LCD_DC, 1);
    pcbkit_gpio_output(LCD_RESET, 1);
    pcbkit_gpio_output(LCD_BACKLIGHT, 0);
    pcbkit_gpio_function(18, FUNC_SPI);
    pcbkit_gpio_function(19, FUNC_SPI);
    printf("LCD SPI %lu Hz\n", (unsigned long)pcbkit_spi_init(SPI0, 25000000));
    /* Hardware reset: low for 10 µs or more, then 120 ms before commands. */
    pcbkit_gpio_put(LCD_RESET, 0);
    sleep_ms(1);
    pcbkit_gpio_put(LCD_RESET, 1);
    sleep_ms(120);
    /* The module's panel is IPS (normally black): colours are true only with inversion on. On
     * the board the module lies turned, its header to the left: the landscape picture is the
     * memory's rows across and its columns upward (row/column exchange, column mirror), RGB. */
    static const uint8_t init[] = {
        0x3a, 1, 0x55,
        0x36, 1, 0x60,
        0,
    };
    for (const uint8_t *p = init; *p; p += 2 + p[1]) lcd_command(p[0], p + 2, p[1]);
    lcd_command(0x21, NULL, 0); /* inversion on */
    lcd_command(0x11, NULL, 0); /* sleep out */
    sleep_ms(120);
    lcd_command(0x29, NULL, 0); /* display on */
    /* Clear the whole panel once, then the game's window only. */
    static const uint8_t all_columns[] = {0, 0, 0x01, 0x3f}, all_pages[] = {0, 0, 0, 0xef};
    lcd_command(0x2a, all_columns, 4);
    lcd_command(0x2b, all_pages, 4);
    static const uint8_t black[64];
    pcbkit_gpio_put(LCD_CS, 0);
    pcbkit_gpio_put(LCD_DC, 0);
    pcbkit_spi_write(SPI0, (const uint8_t[]){0x2c}, 1);
    pcbkit_spi_wait(SPI0);
    pcbkit_gpio_put(LCD_DC, 1);
    for (unsigned i = 0; i < 320 * 240 * 2 / sizeof black; i++) pcbkit_spi_write(SPI0, black, sizeof black);
    pcbkit_spi_wait(SPI0);
    pcbkit_gpio_put(LCD_CS, 1);
    pcbkit_gpio_put(LCD_BACKLIGHT, 1);
}

void I_Init(void) {
    origin = pcbkit_time_us();
}

byte *I_ZoneBase(int *size) {
    *size = 5 * 1024 * 1024;
    return malloc(*size);
}

/* The current tic. A caller that polls without the tic moving is waiting for the next one:
 * after 16 unchanged polls, sleep until it starts. */
int I_GetTime(void) {
    static uint64_t last = UINT64_MAX;
    static unsigned unchanged;
    uint64_t tic = (pcbkit_time_us() - origin) / TIC_US;
    if (tic != last) {
        unchanged = 0;
    } else if (++unchanged >= 16) {
        pcbkit_sleep_until(origin + (tic + 1) * TIC_US);
        tic = (pcbkit_time_us() - origin) / TIC_US;
        unchanged = 0;
    }
    last = tic;
    return (int)tic;
}

void I_StartFrame(void) {}

void I_StartTic(void) {
    static const int keys[BUTTONS] = {KEY_UPARROW, KEY_DOWNARROW, KEY_LEFTARROW, KEY_RIGHTARROW, KEY_RCTRL, ' ', ',', '.', KEY_ESCAPE, KEY_ENTER};
    uint32_t in = REG(SIO_GPIO_IN), pressed = 0;
    for (unsigned i = 0; i < BUTTONS; i++) pressed |= (~in >> button_pins[i] & 1u) << i;
    uint32_t changed = pressed ^ held;
    held = pressed;
    for (unsigned i = 0; i < BUTTONS; i++) {
        if (changed & (1u << i)) {
            event_t event = {.type = pressed & (1u << i) ? ev_keydown : ev_keyup, .data1 = keys[i]};
            D_PostEvent(&event);
        }
    }
}

ticcmd_t *I_BaseTiccmd(void) {
    static ticcmd_t empty;
    return &empty;
}

void I_Quit(void) { exit(0); }

/* The four screens (256,000 bytes) in PSRAM: with the full game's tables and visplanes, SRAM
 * keeps the engine's statics and the stack. */
static PCBKIT_PSRAM byte low[SCREENWIDTH * SCREENHEIGHT * 4];
byte *I_AllocLow(int length) {
    if ((size_t)length <= sizeof low) {
        memset(low, 0, (size_t)length);
        return low;
    }
    return calloc(1, (size_t)length);
}
void I_Tactile(int on, int off, int total) { (void)on; (void)off; (void)total; }

void I_Error(char *format, ...) {
    va_list args;
    va_start(args, format);
    vfprintf(stderr, format, args);
    va_end(args);
    fputc('\n', stderr);
    exit(1);
}

void I_InitGraphics(void) {
    usegamma = 0;
    lcd_start();
}
void I_ShutdownGraphics(void) {}

void I_SetPalette(byte *palette) {
    for (int i = 0; i < 256; i++, palette += 3) palette565[i] = (uint16_t)((palette[0] & 0xf8) << 8 | (palette[1] & 0xfc) << 3 | palette[2] >> 3);
}

void I_SetRelativeMode(boolean enabled) { (void)enabled; }
void I_MarkDirtyLines(int first, int last) { (void)first; (void)last; }
void I_UpdateNoBlit(void) {}

void I_FinishUpdate(void) {
    static const uint8_t columns[] = {0, 0, 0x01, 0x3f}, pages[] = {0, 20, 0, 219};
    lcd_command(0x2a, columns, 4);
    lcd_command(0x2b, pages, 4);
    pcbkit_gpio_put(LCD_CS, 0);
    pcbkit_gpio_put(LCD_DC, 0);
    pcbkit_spi_write(SPI0, (const uint8_t[]){0x2c}, 1);
    pcbkit_spi_wait(SPI0);
    pcbkit_gpio_put(LCD_DC, 1);
    static uint8_t line[SCREENWIDTH * 2];
    const byte *src = screens[0];
    for (int y = 0; y < SCREENHEIGHT; y++) {
        for (int x = 0; x < SCREENWIDTH; x++) {
            uint16_t c = palette565[*src++];
            line[2 * x] = (uint8_t)(c >> 8);
            line[2 * x + 1] = (uint8_t)c;
        }
        pcbkit_spi_write(SPI0, line, sizeof line);
    }
    pcbkit_spi_wait(SPI0);
    pcbkit_gpio_put(LCD_CS, 1);
}
void I_WaitVBL(int count) { (void)count; }
void I_ReadScreen(byte *dest) { memcpy(dest, screens[0], SCREENWIDTH * SCREENHEIGHT); }
void I_BeginRead(void) {}
void I_EndRead(void) {}

/* No audio. Doom's noise propagation (P_NoiseAlert) is gameplay and stays in the engine. */
int snd_SfxVolume = 0, snd_MusicVolume = 0, numChannels = 0;
void S_Init(int sfx, int music) { (void)sfx; (void)music; }
void S_Start(void) {}
void S_StartSound(void *origin_, int id) { (void)origin_; (void)id; }
void S_StartSoundAtVolume(void *origin_, int id, int volume) { (void)origin_; (void)id; (void)volume; }
void S_StopSound(void *origin_) { (void)origin_; }
void S_StartMusic(int id) { (void)id; }
void S_ChangeMusic(int id, int looping) { (void)id; (void)looping; }
void S_StopMusic(void) {}
void S_PauseSound(void) {}
void S_ResumeSound(void) {}
void S_UpdateSounds(void *listener) { (void)listener; }
void S_SetMusicVolume(int volume) { snd_MusicVolume = volume; }
void S_SetSfxVolume(int volume) { snd_SfxVolume = volume; }
void I_ShutdownSound(void) {}

int main(void) {
    for (unsigned i = 0; i < BUTTONS; i++) pcbkit_gpio_input(button_pins[i], 1);
    printf("Doom on doom-07 (RP2350A): %lu Hz, PSRAM %u KiB\n", (unsigned long)pcbkit_sys_hz, (unsigned)(pcbkit_psram_bytes >> 10));
    origin = pcbkit_time_us();
    D_DoomMain();
    return 0;
}
